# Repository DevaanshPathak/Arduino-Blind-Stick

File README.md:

# 👨‍🦯 Arduino-Based Blind Stick with HC-SR04, Buzzer, and LED

This project is a low-cost, Arduino-powered smart stick designed to assist visually impaired individuals by detecting nearby obstacles using an ultrasonic sensor. Alerts are provided through a buzzer and an LED based on object distance.

---

## 📌 Features

- Ultrasonic distance measurement using HC-SR04
- Audible alerts using a buzzer
- Visual alerts using an LED
- Compact design with custom PCB
- Powered by Arduino Uno

---

Slack Username = Devaansh Pathak

---
## 🧩 Components Used

| Component        | Quantity |
|------------------|----------|
| Arduino Uno     | 1        |
| HC-SR04 Sensor   | 1        |
| Buzzer           | 1        |
| LED (5mm)        | 1        |
| 220Ω Resistor    | 1        |
| Jumper Cables(Male to Female)  | As needed |
| Power source (e.g., 9V battery) | 1 |
| Breadboard      | 1        |
| Battery Connector| 1|
---

## 🔌 Circuit Schematic

---

## 🖼️ PCB Layout (2D)

---

## 📷 3D PCB View

---

## ⚙️ Arduino Code

The firmware reads distance from the ultrasonic sensor and triggers alerts if an object is within a safe range (e.g., 25 cm).

```cpp
// defines pins numbers
const int trigPin = 9;
const int echoPin = 10;
const int buzzer = 11;
const int ledPin = 13;

// defines variables
long duration;
int distance;
int safetyDistance;

void setup() {
pinMode(trigPin, OUTPUT); // Sets the trigPin as an Output
pinMode(echoPin, INPUT); // Sets the echoPin as an Input
pinMode(buzzer, OUTPUT);
pinMode(ledPin, OUTPUT);
Serial.begin(9600); // Starts the serial communication
}

void loop() {
// Clears the trigPin
digitalWrite(trigPin, LOW);
delayMicroseconds(2);

// Sets the trigPin on HIGH state for 10 micro seconds
digitalWrite(trigPin, HIGH);
delayMicroseconds(10);
digitalWrite(trigPin, LOW);

// Reads the echoPin, returns the sound wave travel time in microseconds
duration = pulseIn(echoPin, HIGH);

// Calculating the distance
distance= duration*0.034/2;

safetyDistance = distance;
if (safetyDistance <= 25){
  digitalWrite(buzzer, HIGH);
  digitalWrite(ledPin, HIGH);
}
else{
  digitalWrite(buzzer, LOW);
  digitalWrite(ledPin, LOW);
}

// Prints the distance on the Serial Monitor
Serial.print("Distance: ");
Serial.println(distance);
}

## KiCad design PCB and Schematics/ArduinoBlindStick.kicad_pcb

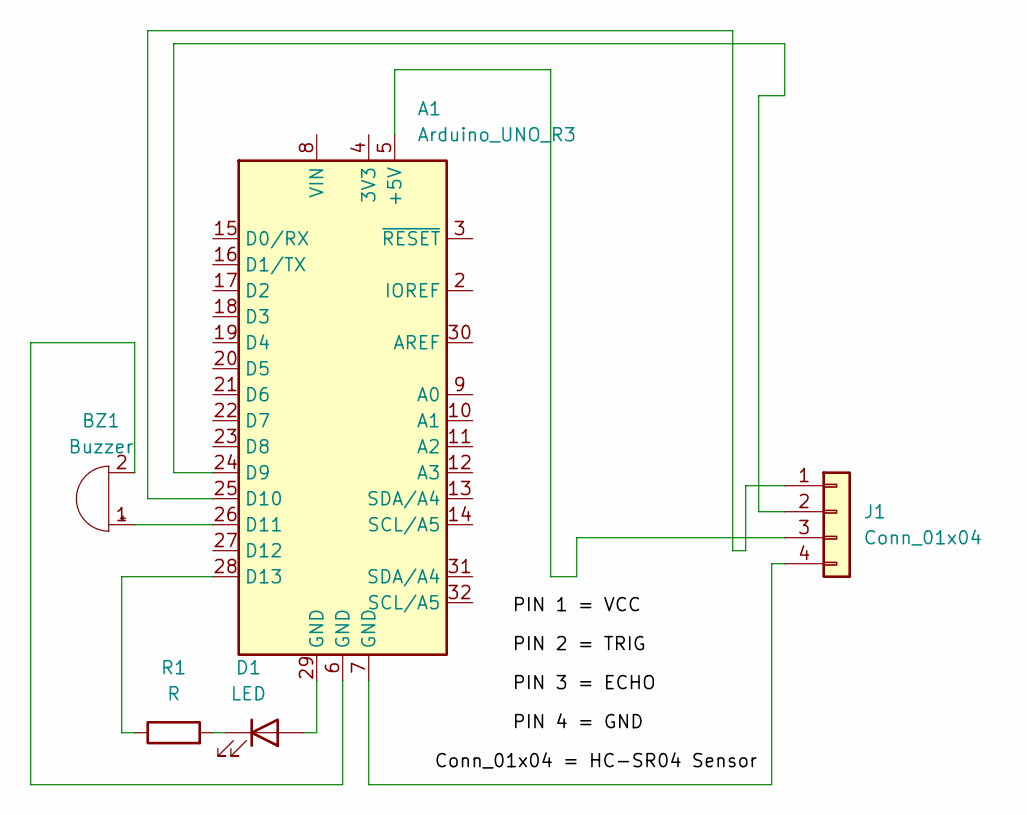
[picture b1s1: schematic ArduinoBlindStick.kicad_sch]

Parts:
A1: Arduino_UNO_R3
BZ1: Buzzer; Buzzer_12x9.5RM7.6
D1: LED; LED_D1.8mm_W1.8mm_H2.4mm_Horizontal_O1.27mm_Z1.6mm
J1: Conn_01x04; PinHeader_1x04_P1.00mm_Horizontal
R1: R; R_0201_0603Metric

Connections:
unnamed: A1.5 (+5V), J1.3
unnamed: A1.24 (D9), J1.2
unnamed: A1.25 (D10), J1.1
unnamed: A1.26 (D11), BZ1.1 (+)
unnamed: A1.28 (D13), R1.1
unnamed: A1.6 (GND), BZ1.2 (-)
unnamed: A1.29 (GND), D1.2 (A)
unnamed: D1.1 (K), R1.2
unnamed: A1.7 (GND), J1.4

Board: 2 copper layers, 5 parts (0 on the bottom side), 9 nets, no tracks yet.

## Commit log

2025-06-17 Did good stuff
